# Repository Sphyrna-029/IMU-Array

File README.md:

# IMU-Array
A cheap MPU650 IMU array for experimenting with inertial navigation.

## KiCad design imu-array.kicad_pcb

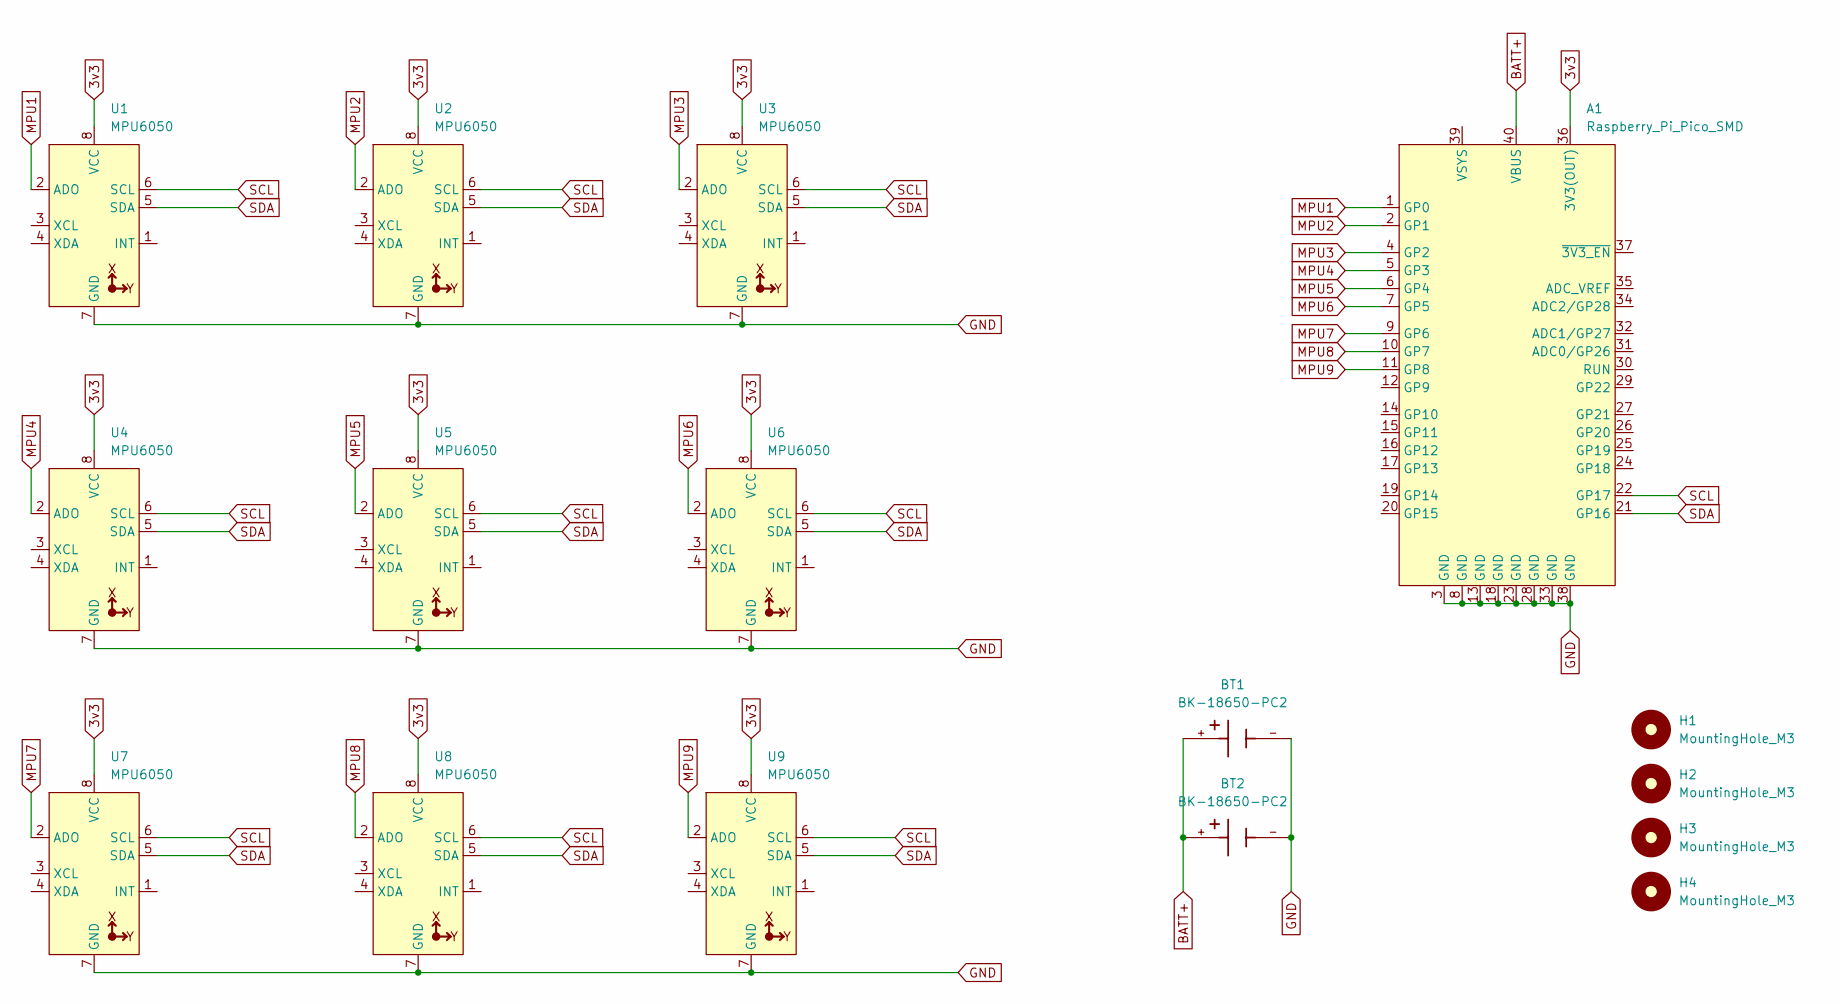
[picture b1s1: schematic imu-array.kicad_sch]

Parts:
A1: Raspberry_Pi_Pico_SMD; raspberry_pi_pico_SMD
BT1, BT2: BK-18650-PC2; BAT_BK-18650-PC2; PARTREV F
H1, H2, H3, H4: MountingHole_M3; MountingHole_3.2mm_M3
U1, U2, U3, U4, U5, U6, U7, U8, U9: MPU6050; MPU6050_Breakout

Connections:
3v3: A1.36 (3V3(OUT)), U1.8 (VCC), U2.8 (VCC), U3.8 (VCC), U4.8 (VCC), U5.8 (VCC), U6.8 (VCC), U7.8 (VCC), U8.8 (VCC), U9.8 (VCC)
BATT+: A1.40 (VBUS), BT1.+, BT2.+
GND: A1.3 (GND), A1.8 (GND), A1.13 (GND), A1.18 (GND), A1.23 (GND), A1.28 (GND), A1.33 (GND), A1.38 (GND), BT1.-, BT2.-, U1.7 (GND), U2.7 (GND), U3.7 (GND), U4.7 (GND), U5.7 (GND), U6.7 (GND), U7.7 (GND), U8.7 (GND), U9.7 (GND)
MPU1: A1.1 (GP0), U1.2 (ADO)
MPU2: A1.2 (GP1), U2.2 (ADO)
MPU3: A1.4 (GP2), U3.2 (ADO)
MPU4: A1.5 (GP3), U4.2 (ADO)
MPU5: A1.6 (GP4), U5.2 (ADO)
MPU6: A1.7 (GP5), U6.2 (ADO)
MPU7: A1.9 (GP6), U7.2 (ADO)
MPU8: A1.10 (GP7), U8.2 (ADO)
MPU9: A1.11 (GP8), U9.2 (ADO)
SCL: A1.22 (GP17), U1.6 (SCL), U2.6 (SCL), U3.6 (SCL), U4.6 (SCL), U5.6 (SCL), U6.6 (SCL), U7.6 (SCL), U8.6 (SCL), U9.6 (SCL)
SDA: A1.21 (GP16), U1.5 (SDA), U2.5 (SDA), U3.5 (SDA), U4.5 (SDA), U5.5 (SDA), U6.5 (SDA), U7.5 (SDA), U8.5 (SDA), U9.5 (SDA)

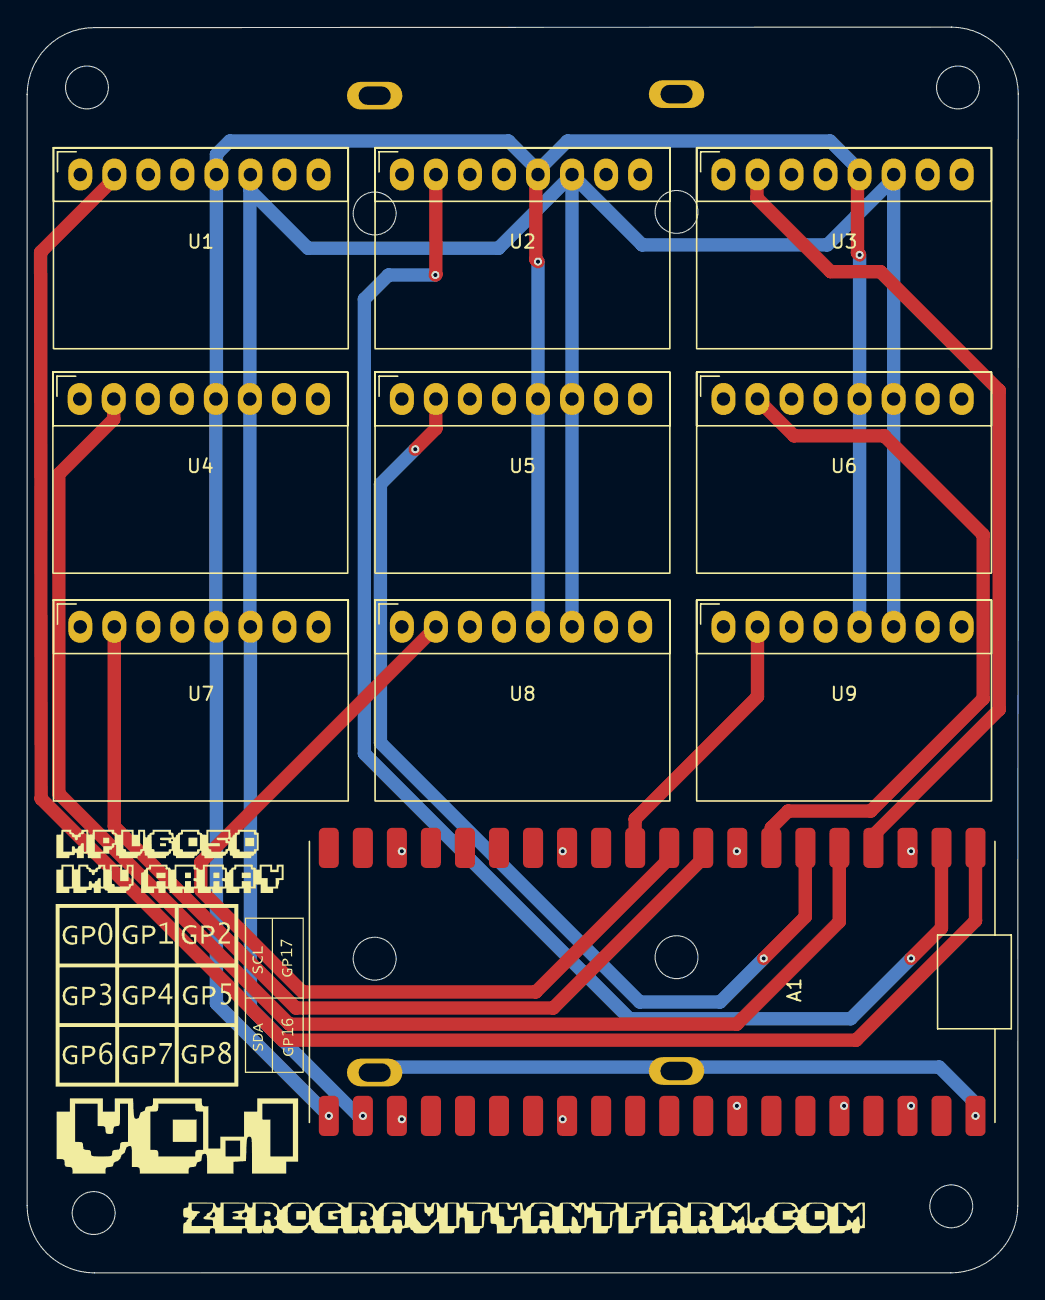
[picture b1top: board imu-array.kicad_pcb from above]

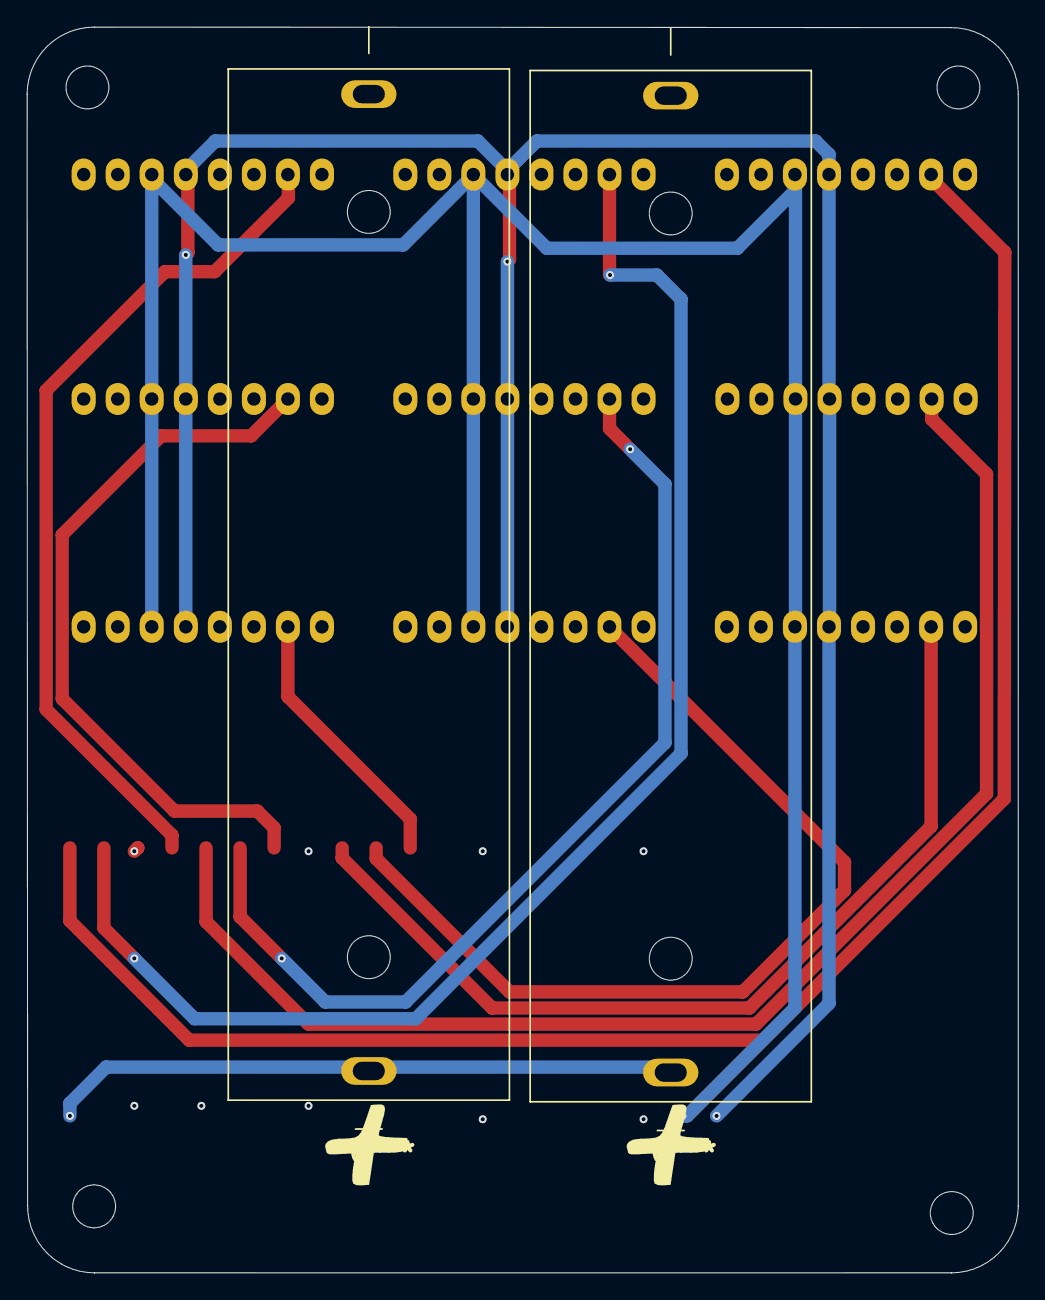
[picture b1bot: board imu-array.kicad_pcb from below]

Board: 4 copper layers, 74.0 x 93.0 mm, 16 parts (2 on the bottom side), 14 nets.

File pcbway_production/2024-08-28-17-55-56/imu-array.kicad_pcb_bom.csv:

Designator,Quantity,Value,Footprint,Package,MPN,DNP,Mount_Type,Description,MF,MAXIMUM_PACKAGE_HEIGHT,Price,Check_prices,STANDARD,PARTREV,SnapEDA_Link,MP,Description_1,Availability,MANUFACTURER
A1,1,Raspberry_Pi_Pico_SMD,raspberry_pi_pico_SMD,,,,smt,Development Board with RP2040 MCU,,,,,,,,,,,
"BT1, BT2",2,BK-18650-PC2,BAT_BK-18650-PC2,None,,,tht,,MPD (Memory Protection Devices),21.41 mm,None,https://www.snapeda.com/parts/BK-18650-PC2/Memory+Protection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,Manufacturer Recommendations,F,https://www.snapeda.com/parts/BK-18650-PC2/Memory+Protection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,BK-18650-PC2,"
Battery Holder (Open) 18650 1 Cell PC Pin
",In Stock,MPD
"H1, H2, H3, H4",4,MountingHole_M3,MountingHole_3.2mm_M3,,,,tht,3.2mm Diameter Mounting Hole (M3),,,,,,,,,,,
"U1, U2, U3, U4, U5, U6, U7, U8, U9",9,MPU6050,MPU6050_Breakout,,,,tht,"MPU6050 Breakout Board, 6-Axis Motion Sensor, Gyroscope, Accelerometer",,,,,,,,,,,
